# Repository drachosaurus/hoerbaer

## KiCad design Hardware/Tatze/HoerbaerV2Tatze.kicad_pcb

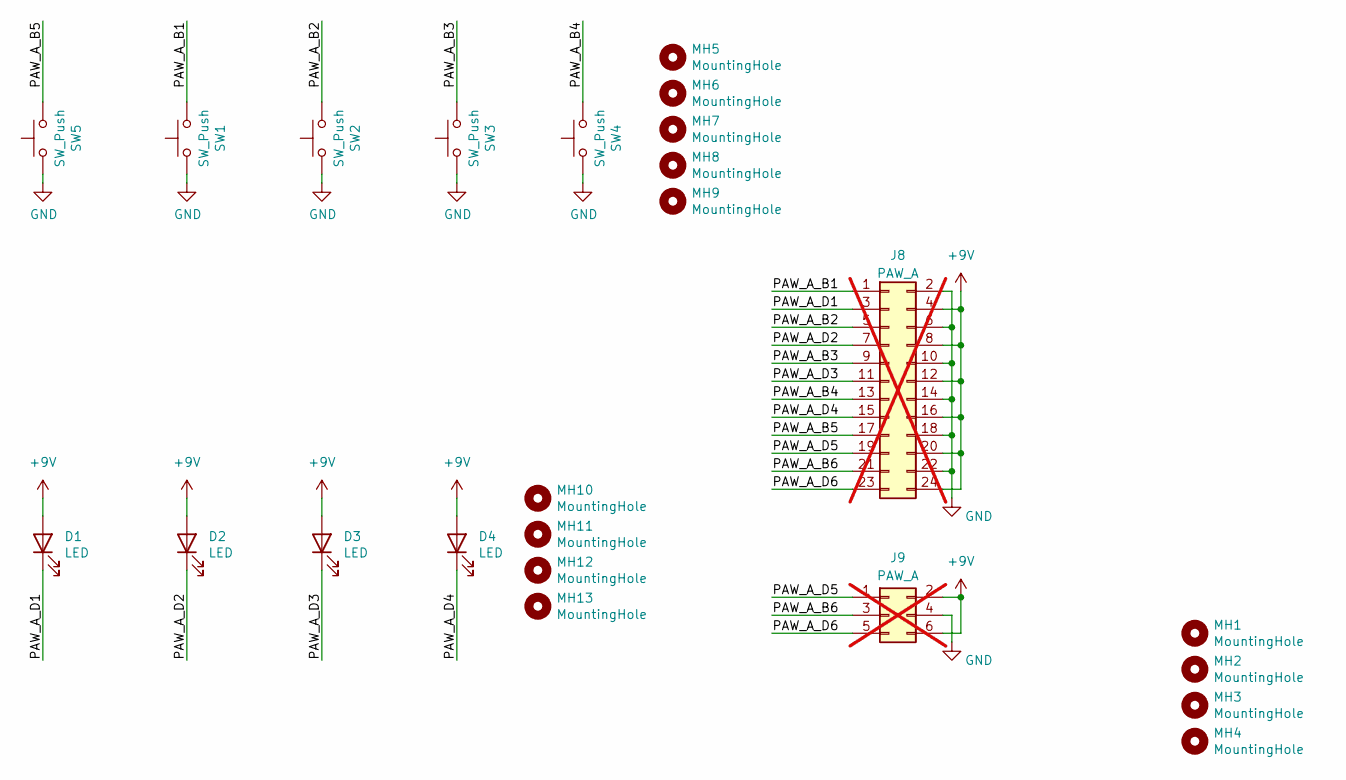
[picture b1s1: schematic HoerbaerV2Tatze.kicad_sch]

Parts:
D1, D2, D3, D4: LED; LED_D3.0mm
J8: PAW_A; PinHeader_2x12_P2.54mm_Vertical; JLCPCB Rotation Offset 90; not fitted
J9: PAW_A; PinHeader_2x03_P2.54mm_Vertical; JLCPCB Rotation Offset 90; not fitted
MH1, MH2, MH3, MH4: MountingHole; MountingHole_3.2mm_M3
MH5, MH6, MH7, MH8, MH9, MH10, MH11, MH12, MH13: MountingHole; MountingHole_2.1mm
SW1, SW2, SW3, SW4, SW5: SW_Push; SW_PUSH_6mm

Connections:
+9V: D1.2 (A), D2.2 (A), D3.2 (A), D4.2 (A), J8.4, J8.8, J8.12, J8.16, J8.20, J8.24, J9.2, J9.6
/PAW_A_B1: J8.1, SW1.2
/PAW_A_B2: J8.5, SW2.2
/PAW_A_B3: J8.9, SW3.2
/PAW_A_B4: J8.13, SW4.2
/PAW_A_B5: J8.17, SW5.2
/PAW_A_B6: J8.21, J9.3
/PAW_A_D1: D1.1 (K), J8.3
/PAW_A_D2: D2.1 (K), J8.7
/PAW_A_D3: D3.1 (K), J8.11
/PAW_A_D4: D4.1 (K), J8.15
/PAW_A_D5: J8.19, J9.1
/PAW_A_D6: J8.23, J9.5
GND: J8.2, J8.6, J8.10, J8.14, J8.18, J8.22, J9.4, SW1.1, SW2.1, SW3.1, SW4.1, SW5.1

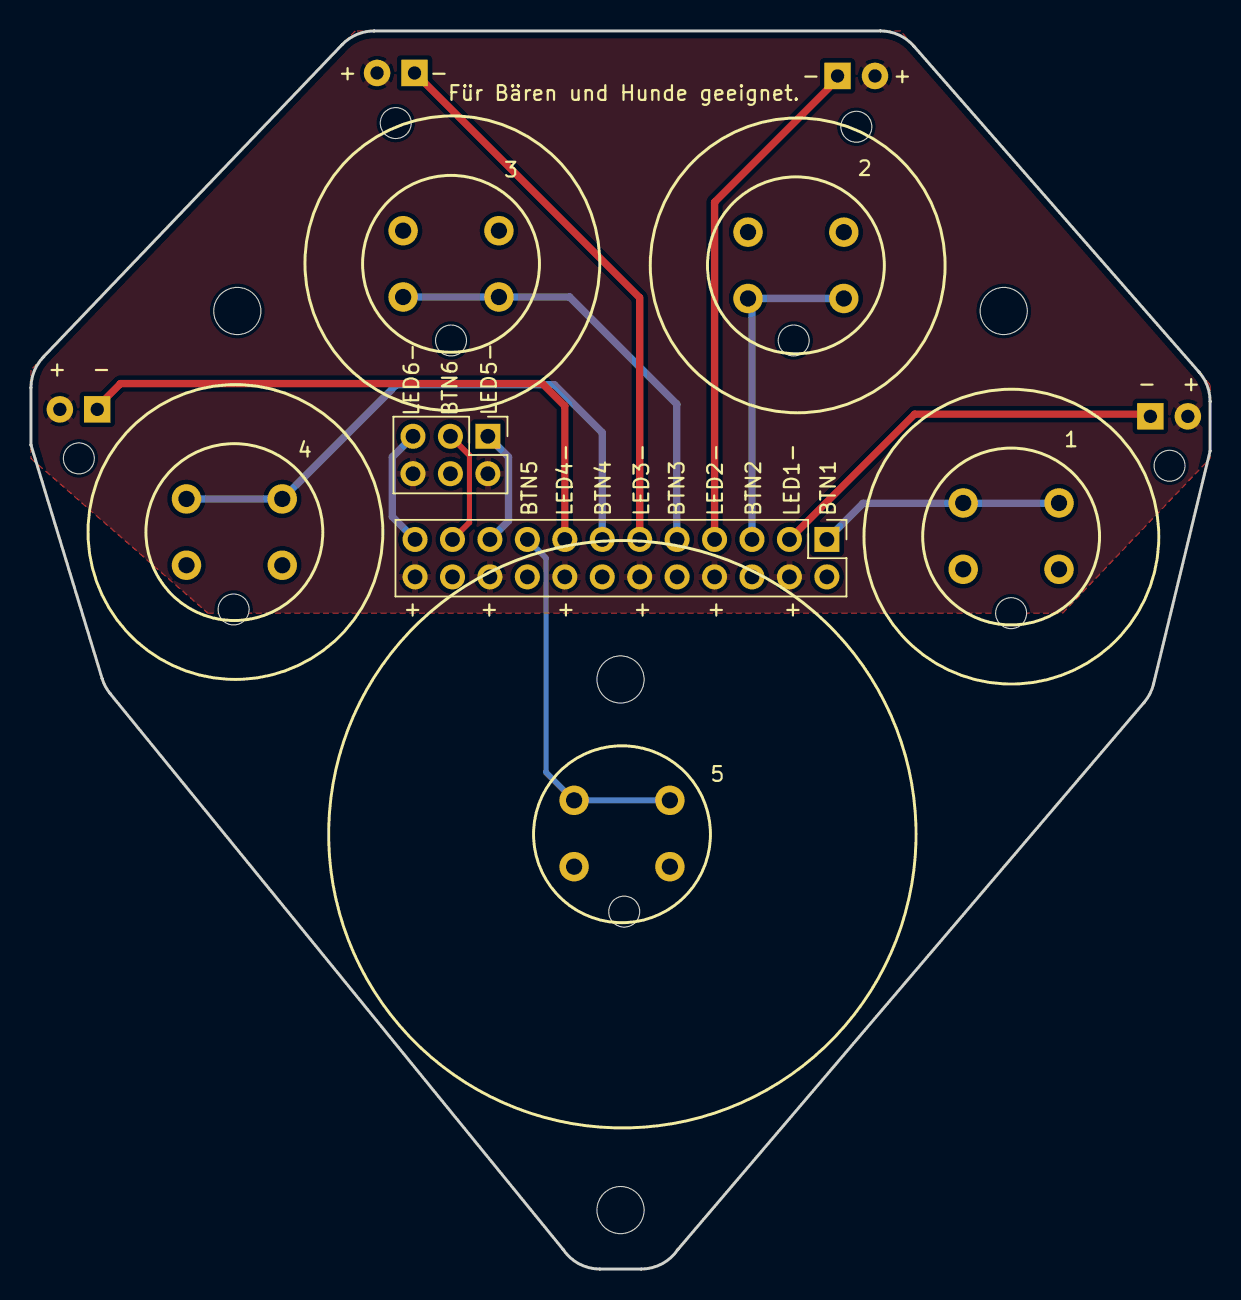
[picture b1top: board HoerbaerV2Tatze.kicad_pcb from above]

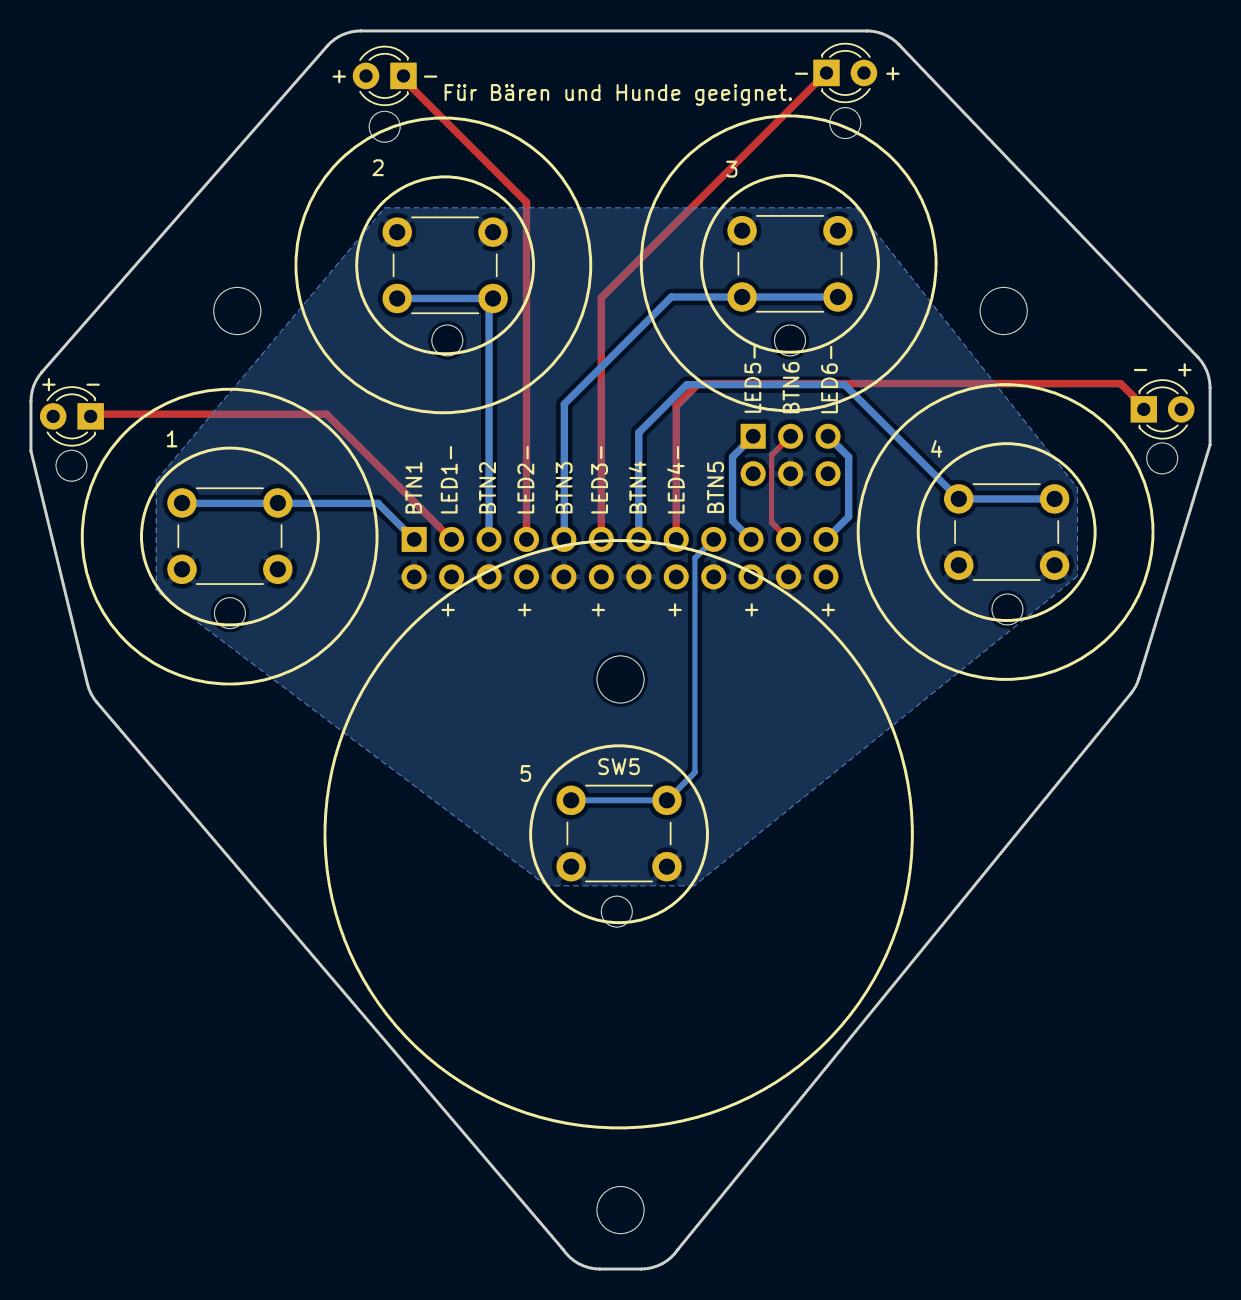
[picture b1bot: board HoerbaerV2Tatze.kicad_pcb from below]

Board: 2 copper layers, 80.0 x 84.0 mm, 24 parts (9 on the bottom side), 14 nets.

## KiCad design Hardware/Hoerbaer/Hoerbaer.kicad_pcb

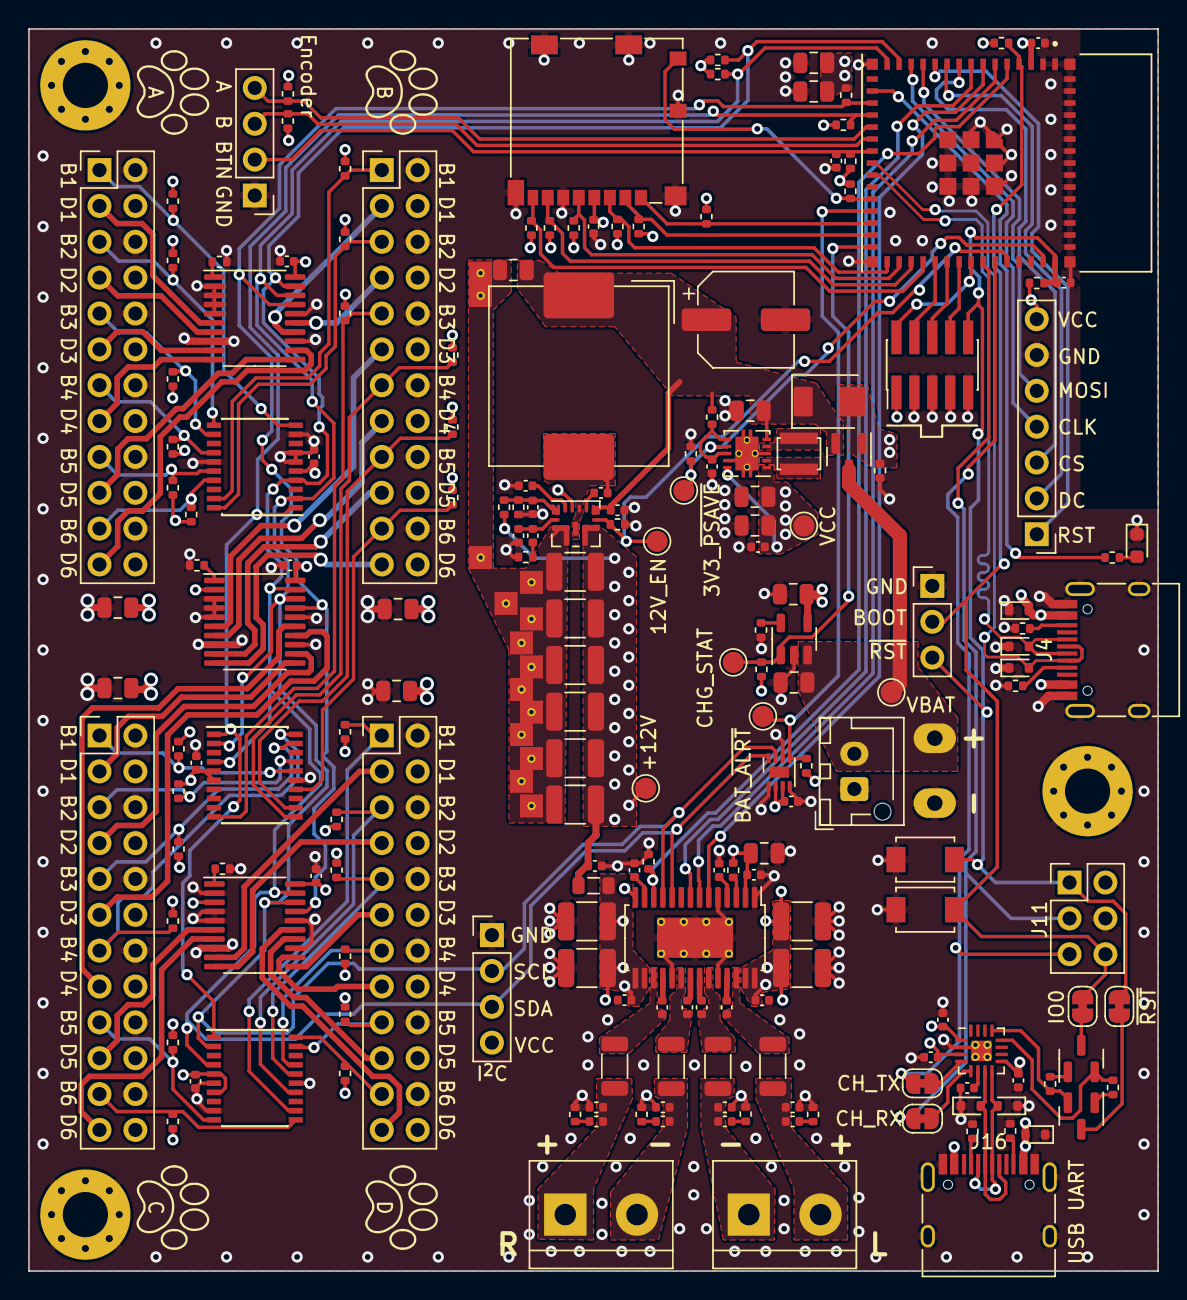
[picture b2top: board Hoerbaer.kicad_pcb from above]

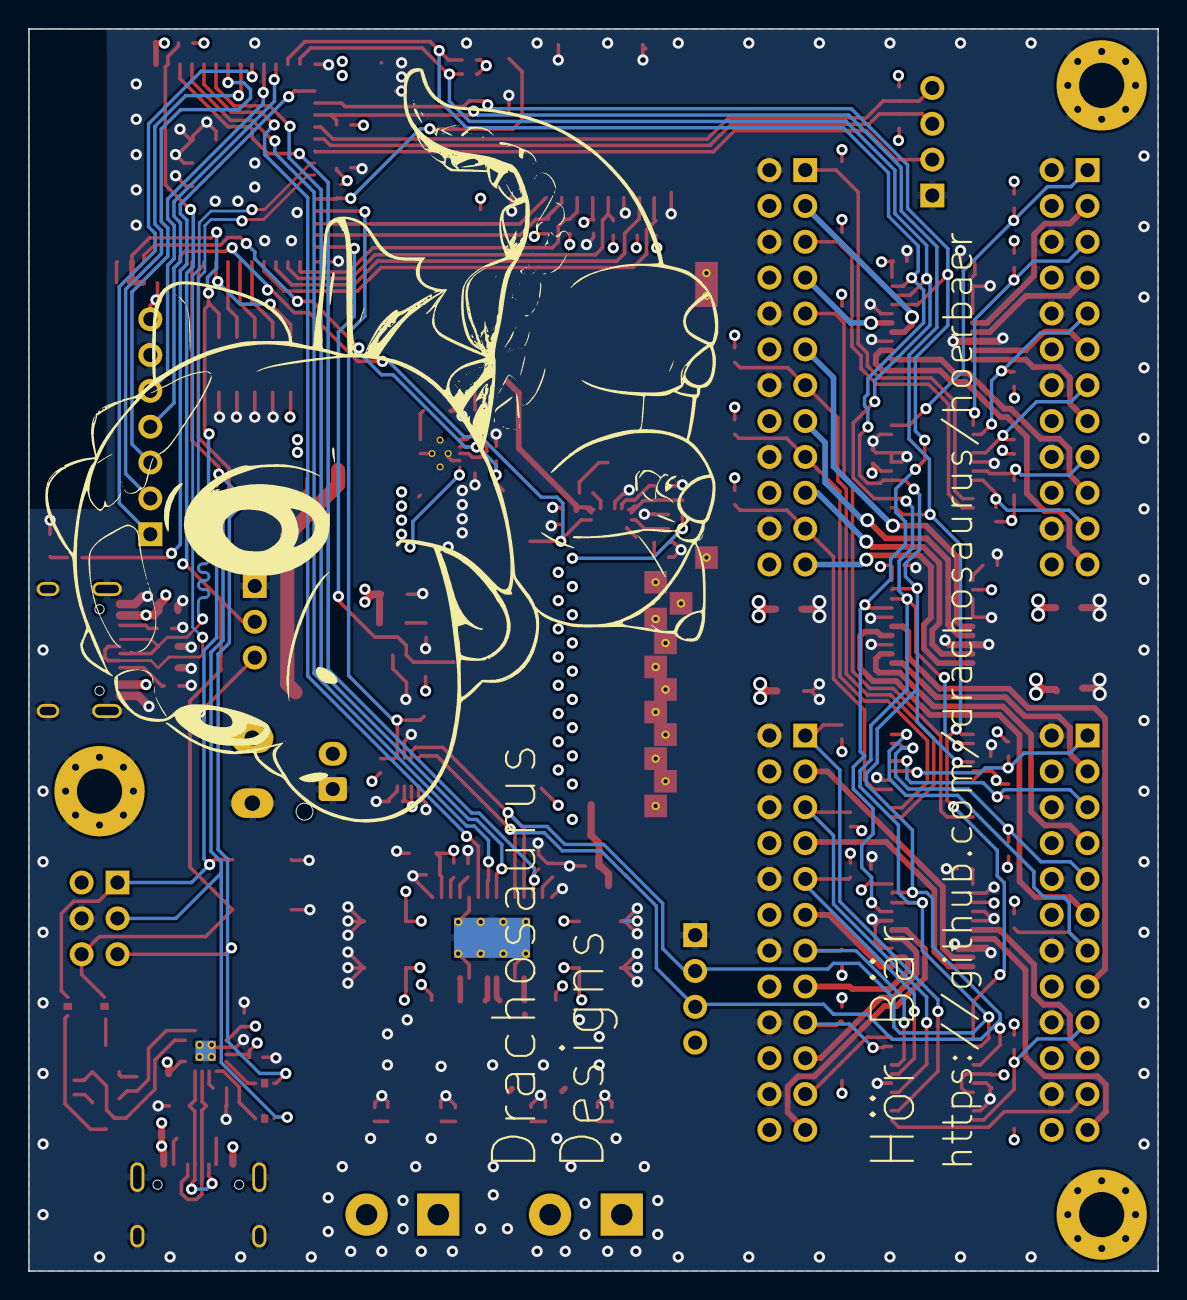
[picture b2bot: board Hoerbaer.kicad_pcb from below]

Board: 4 copper layers, 80.0 x 88.0 mm, 209 parts (14 on the bottom side), 143 nets.

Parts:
C1, C4, C5, C15, C20, C34, C35: 1µF, 10V; C_0402_1005Metric
C2, C3, C13, C14, C16, C22, C23, C24, C26, C65: 10µF; C_0805_2012Metric
C6, C7, C8, C9, C10, C11, C12, C19, C21, C25, C36, C43, C50, C58, C63, C64: 100nF; C_0402_1005Metric
C17, C18, C55: 4.7µF, 10V; C_0805_2012Metric
C27, C28, C29, C30, C31, C32, C37, C38, C44, C45: 22µF, low ESR; C_1210_3225Metric
C33, C46, C47, C48, C49, C51, C52, C53, C54: 2.2nF; C_0402_1005Metric
C39, C40, C41, C42: 220nF; C_0402_1005Metric
C56, C57: 1uF; C_0402_1005Metric
C59, C61: 27pF; C_0402_1005Metric
C60: 4.7nF; C_0402_1005Metric
C62: 47µF; CP_Elec_6.3x5.9
D1, D2, D5, D6, D7, D8: LESD5D5.0CT1G; D_SOD-523
D3: S54BF
D4: GREEN; LED_0603_1608Metric
FB1: 100Ω@100MHz, 3A; L_0805_2012Metric
FB2, FB3, FB4, FB5: 300Ω@100MHz, 3A; L_1206_3216Metric
H1, H2, H3: MountingHole_Pad; MountingHole_3.2mm_M3_Pad_Via
J1: I2C; PinHeader_1x04_P2.54mm_Vertical
J2: DISPLAY; PinHeader_1x07_P2.54mm_Vertical
J3: uSD; microSD_HC_Molex_104031-0811
J4: USB1; USB_C_Receptacle_HRO_TYPE-C-31-M-12
J5: ENCODER; PinHeader_1x04_P2.54mm_Vertical
J6: PAW_A; PinHeader_2x12_P2.54mm_Vertical
J7: PAW_B; PinHeader_2x12_P2.54mm_Vertical
J8: PAW_C; PinHeader_2x12_P2.54mm_Vertical
J9: PAW_D; PinHeader_2x12_P2.54mm_Vertical
J10: Battery 1S Li-Ion; SolderWire-0.5sqmm_1x02_P4.6mm_D0.9mm_OD2.1mm
J11: UART; PinHeader_2x03_P2.54mm_Vertical
J12: Battery 1S Li-Ion; JST_XH_B2B-XH-AM_1x02_P2.50mm_Vertical
J13: JTAG; PinHeader_2x05_P1.27mm_Vertical_SMD
J14: Speaker_L; TerminalBlock_bornier-2_P5.08mm
J15: Speaker_R; TerminalBlock_bornier-2_P5.08mm
J16: USB2_UART; USB_C_Receptacle_HRO_TYPE-C-31-M-12
J17: RST_BOOT; PinHeader_1x03_P2.54mm_Vertical
JP1: CH_TX; SolderJumper-2_P1.3mm_Bridged_RoundedPad1.0x1.5mm
JP2: CH_RX; SolderJumper-2_P1.3mm_Bridged_RoundedPad1.0x1.5mm
JP3: ~{RST}; SolderJumper-2_P1.3mm_Bridged_RoundedPad1.0x1.5mm
JP4: IO0; SolderJumper-2_P1.3mm_Bridged_RoundedPad1.0x1.5mm
L1: 2.2µH; L_Murata_LQH3NPN
L2: 4.7uH, 14A; L_TDK_SPM12565
NT1, NT2, NT3, NT4, NT5, NT6, NT7, NT8, NT9, NT10, NT11, NT12, NT13, NT14: GNDs; NetTie-2_Via
Q1: DMG3415UQ-7; SOT-23
Q5, Q6: S8050; SOT-23
R1, R2, R3, R4, R7, R8, R9, R10, R11, R12, R13, R14, R15, R16, R17, R18, R19, R20, R21, R22, R23, R24, R25, R26, R27, R28, R29, R30, R31, R32, R33, R34, R35, R36, R37, R38, R39, R40, R41, R42, R46, R50, R51, R52, R54, R61, R69, R70: 10kΩ; R_0402_1005Metric
R5, R6, R56, R67, R68: 5.1kΩ; R_0402_1005Metric
R43, R44, R45, R49: 2kΩ; R_0402_1005Metric
R47: 100Ω; R_0402_1005Metric
R48: 100kΩ; R_0402_1005Metric
R53: 191kΩ; R_0402_1005Metric
R55: 47kΩ; R_0402_1005Metric
R62: 4.7kΩ; R_0402_1005Metric
R63, R64, R65, R66: 68Ω; R_0402_1005Metric
SW1: RESET; SW_ TS-1088-AR02016
SW2: PROG; SW_ TS-1088-AR02016
TP4: VCC; TestPoint_Pad_D1.5mm
TP5: VBAT; TestPoint_Pad_D1.5mm
TP6: 3V3_~{PSAVE}; TestPoint_Pad_D1.5mm
TP7: 12V_EN; TestPoint_Pad_D1.5mm
TP8: CHG_STAT; TestPoint_Pad_D1.5mm
TP9: BAT_~{ALRT}; TestPoint_Pad_D1.5mm
TP10: +12V; TestPoint_Pad_D1.5mm
U1: ESP32 S3 MINI; XCVR_ESP32-S3-MINI-1-N8
U2, U3, U4: PCF8574APWR; SSOP-20_4.4x6.5mm_P0.65mm
U5, U6, U7: TLC59108xPW; TSSOP-20_4.4x6.5mm_P0.65mm
U8: MCP73831T-2ACI/OT (4.2V); SOT-23-5
U9: TPS63001; Texas_DRC0010J_ThermalVias
U10: TAS5805M; HTSSOP-28-1EP_4.4x9.7mm_P0.65mm_EP2.85x5.4mm_ThermalVias
U11: CH343P; QFN-16-1EP_3x3mm_P0.5mm_EP1.45x1.45mm_ThermalVias
U12: MAX17048G; TDFN-8-1EP_MAXIM
U13: TPS61288; Texas_VQFN-HR-20_3x2.5mm_P0.5mm_RQQ0011A

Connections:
+12V: C22.1, C23.1, C24.1, C27.1, C28.1, C29.1, C30.1, C31.1, C32.1, C33.1, C65.1, FB1.1, J6.4, J6.8, J6.12, J6.16, J6.20, J6.24, J7.4, J7.8, J7.12, J7.16, J7.20, J7.24, J8.4, J8.8, J8.12, J8.16, J8.20, J8.24, J9.4, J9.8, J9.12, J9.16, J9.20, J9.24, R53.1, TP10.1, U13.5 (VOUT)
+BATT: C17.1, C19.1, J10.2, J12.2, Q1.3 (D), TP5.1, U8.3 (VBAT), U12.2 (CELL), U12.3 (VDD)
/3V3_~PSAVE: R46.1, TP6.1, U1.44 (IO46), U9.7 (PS/SYNC)
/12V_EN: R52.1, TP7.1, U1.41 (IO45), U13.6 (EN)
/Audio/AMP_OUT_A+: C39.2, FB2.1, U10.26 (OUT_A+)
/Audio/AMP_OUT_A-: C40.2, FB3.1, U10.23 (OUT_A-)
/Audio/AMP_OUT_B+: C41.2, FB4.1, U10.17 (OUT_B+)
/Audio/AMP_OUT_B-: C42.2, FB5.1, U10.20 (OUT_B-)
/Audio/PVDD: C36.1, C37.1, C38.1, C43.1, C44.1, C45.1, FB1.2, U10.15 (PVDD), U10.16 (PVDD), U10.27 (PVDD), U10.28 (PVDD)
/Audio/SPEAKER_A+: C46.1, C51.1, FB2.2, J14.2
/Audio/SPEAKER_A-: C47.1, C52.1, FB3.2, J14.1
/Audio/SPEAKER_B+: C48.1, C53.1, FB4.2, J15.1
/Audio/SPEAKER_B-: C49.1, C54.1, FB5.2, J15.2
/BAT_~ALERT: R51.2, TP9.1, U1.27 (IO47), U12.5 (~ALRT)
/CHG_STAT: R50.2, TP8.1, U1.30 (IO48), U8.1 (STAT)
/CODEC_~PDN: R61.2, U1.5 (IO1), U10.12 (~PDN)
/DISP_CS: J2.3, U1.9 (IO5)
/DISP_DC: J2.2, U1.10 (IO6)
/DISP_RST: J2.1, U1.11 (IO7)
/ENC_A: J5.4, R8.2, U1.20 (IO16)
/ENC_B: J5.3, R10.2, U1.21 (IO17)
/ENC_BTN: C64.1, J5.2, R13.2, U1.22 (IO18)
/HBI/PAW_A_B1: J6.1, R19.2, U2.10 (P0)
/HBI/PAW_A_B2: J6.5, R22.2, U2.11 (P1)
/HBI/PAW_A_B3: J6.9, R25.2, U2.12 (P2)
/HBI/PAW_A_B4: J6.13, R28.2, U2.14 (P3)
/HBI/PAW_A_B5: J6.17, R31.2, U2.16 (P4)
/HBI/PAW_A_B6: J6.21, R34.2, U2.17 (P5)
/HBI/PAW_A_D1: J6.3, U5.6 (~OUT0)
/HBI/PAW_A_D2: J6.7, U5.7 (~OUT1)
/HBI/PAW_A_D3: J6.11, U5.9 (~OUT2)
/HBI/PAW_A_D4: J6.15, U5.10 (~OUT3)
/HBI/PAW_A_D5: J6.19, U5.11 (~OUT4)
/HBI/PAW_A_D6: J6.23, U5.12 (~OUT5)
/HBI/PAW_B_B1: J7.1, R37.2, U2.19 (P6)
/HBI/PAW_B_B2: J7.5, R40.2, U2.20 (P7)
/HBI/PAW_B_B3: J7.9, R20.2, U3.10 (P0)
/HBI/PAW_B_B4: J7.13, R23.2, U3.11 (P1)
/HBI/PAW_B_B5: J7.17, R26.2, U3.12 (P2)
/HBI/PAW_B_B6: J7.21, R29.2, U3.14 (P3)
/HBI/PAW_B_D1: J7.3, U5.14 (~OUT6)
/HBI/PAW_B_D2: J7.7, U5.15 (~OUT7)
/HBI/PAW_B_D3: J7.11, U6.6 (~OUT0)
/HBI/PAW_B_D4: J7.15, U6.7 (~OUT1)
/HBI/PAW_B_D5: J7.19, U6.9 (~OUT2)
/HBI/PAW_B_D6: J7.23, U6.10 (~OUT3)
/HBI/PAW_C_B1: J8.1, R32.2, U3.16 (P4)
/HBI/PAW_C_B2: J8.5, R35.2, U3.17 (P5)
/HBI/PAW_C_B3: J8.9, R38.2, U3.19 (P6)
/HBI/PAW_C_B4: J8.13, R41.2, U3.20 (P7)
/HBI/PAW_C_B5: J8.17, R21.2, U4.10 (P0)
/HBI/PAW_C_B6: J8.21, R24.2, U4.11 (P1)
/HBI/PAW_C_D1: J8.3, U6.11 (~OUT4)
/HBI/PAW_C_D2: J8.7, U6.12 (~OUT5)
/HBI/PAW_C_D3: J8.11, U6.14 (~OUT6)
/HBI/PAW_C_D4: J8.15, U6.15 (~OUT7)
/HBI/PAW_C_D5: J8.19, U7.6 (~OUT0)
/HBI/PAW_C_D6: J8.23, U7.7 (~OUT1)
/HBI/PAW_D_B1: J9.1, R27.2, U4.12 (P2)
/HBI/PAW_D_B2: J9.5, R30.2, U4.14 (P3)
/HBI/PAW_D_B3: J9.9, R33.2, U4.16 (P4)
/HBI/PAW_D_B4: J9.13, R36.2, U4.17 (P5)
/HBI/PAW_D_B5: J9.17, R39.2, U4.19 (P6)
/HBI/PAW_D_B6: J9.21, R42.2, U4.20 (P7)
/HBI/PAW_D_D1: J9.3, U7.9 (~OUT2)
/HBI/PAW_D_D2: J9.7, U7.10 (~OUT3)
/HBI/PAW_D_D3: J9.11, U7.11 (~OUT4)
/HBI/PAW_D_D4: J9.15, U7.12 (~OUT5)
/HBI/PAW_D_D5: J9.19, U7.14 (~OUT6)
/HBI/PAW_D_D6: J9.23, U7.15 (~OUT7)
/HBI_INT: R17.2, U1.19 (IO15), U2.1 (~INT), U3.1 (~INT), U4.1 (~INT)
/HBI_RST: R18.2, U1.18 (IO14), U5.17 (~RESET), U6.17 (~RESET), U7.17 (~RESET)
/I2C1_SCL: J1.2, R1.2, U1.15 (IO11), U2.2 (SCL), U3.2 (SCL), U4.2 (SCL), U5.18 (SCL), U6.18 (SCL), U7.18 (SCL), U10.11 (SCL), U12.7 (SCL)
/I2C1_SDA: J1.3, R2.2, U1.14 (IO10), U2.4 (SDA), U3.4 (SDA), U4.4 (SDA), U5.19 (SDA), U6.19 (SDA), U7.19 (SDA), U10.10 (SDA), U12.8 (SDA)
/I2S1_BCLK: U1.6 (IO2), U10.7 (SCLK)
/I2S1_DOUT: U1.8 (IO4), U10.8 (SDIN)
/I2S1_WS: U1.7 (IO3), U10.6 (LRCLK)
/JTAG_TCK: J13.4, U1.35 (IO39)
/JTAG_TDI: J13.8, U1.37 (IO41)
/JTAG_TDO: J13.6, U1.36 (IO40)
/JTAG_TMS: J13.2, U1.38 (IO42)
/MCU_IO0: J11.6, J17.2, JP4.1 (A), R16.2, SW2.2, U1.4 (IO0)
/MCU_RXD: J11.5, JP1.1 (A), U1.40 (RXD0)
/MCU_TXD: J11.3, JP2.1 (A), U1.39 (TXD0)
/MCU_~RST: C5.1, J11.1, J13.10, J17.3, JP3.1 (A), R15.2, SW1.2, U1.45 (EN)
/Power/3V3_L1: L1.1, U9.4 (L1)
/Power/3V3_L2: L1.2, U9.2 (L2)
/Power/12V_SW: C21.1, L2.2, U13.4 (SW), U13.9 (SW)
/Power/SWITCHER_VIN: C13.1, C25.1, C26.1, C62.1, D3.1 (K), L2.1, Q1.2 (S), R47.1, U9.5 (VIN), U13.7 (VIN)
/SD_CLK: J3.5 (CLK), R9.2, U1.32 (IO36)
/SD_CMD: J3.3 (CMD), R7.2, U1.31 (IO35)
/SD_D0: J3.7 (DAT0), R11.2, U1.33 (IO37)
/SD_D1: J3.8 (DAT1), R12.2, U1.34 (IO38)
/SD_D2: J3.1 (DAT2), R3.2, U1.28 (IO33)
/SD_D3: J3.2 (DAT3/CD), R4.2, U1.29 (IO34)
/SD_DET: J3.10 (DET_A), R14.2, U1.26 (IO26)
/SPI2_CLK: J2.4, U1.13 (IO9)
/SPI2_MOSI: J2.5, U1.12 (IO8)
/USB1_D+: D2.2 (A2), J4.A6 (D+), J4.B6 (D+), U1.24 (IO20)
/USB1_D-: D1.2 (A2), J4.A7 (D-), J4.B7 (D-), U1.23 (IO19)
/USB_UART/USB2_D+: D7.2 (A2), J16.A6 (D+), J16.B6 (D+), U11.7 (UD+)
/USB_UART/USB2_D-: D5.2 (A2), J16.A7 (D-), J16.B7 (D-), U11.8 (UD-)
/USB_UART/USB2_VBUS: C57.1, C63.1, D6.2 (A2), J16.A4 (VBUS), J16.A9 (VBUS), J16.B4 (VBUS), J16.B9 (VBUS), U11.3 (VDD5), U11.9 (VBUS)
/USB_UART/USB_UART_MCU_GPIO0_CHIP: JP4.2 (B), Q6.3 (C)
/USB_UART/USB_UART_MCU_~RST_CHIP: JP3.2 (B), Q5.3 (C)
/USB_UART/USB_UART_RXD_CHIP: JP2.2 (B), U11.5 (RXD)
/USB_UART/USB_UART_TXD_CHIP: JP1.2 (B), U11.4 (TXD)
GND: C1.2, C2.2, C3.2, C4.2, C5.2, C6.2, C7.2, C8.2, C9.2, C10.2, C11.2, C12.2, C13.2, C14.2, C15.2, C16.2, C17.2, C18.2, C19.2, C20.2, C22.2, C23.2, C24.2, C25.2, C33.2, C34.1, C35.1, C36.2, C37.2, C38.2, C43.2, C44.2, C45.2, C46.2, C47.2, C48.2, C49.2, C50.2, C55.2, C56.2, C57.2, C58.2, C59.2, C61.2, C62.2, C63.2, C64.2, C65.2, D1.1 (A1), D2.1 (A1), D4.1 (K), D5.1 (A1), D6.1 (A1), D7.1 (A1), D8.1 (A1), H1.1, H2.1, H3.1, J1.1, J2.6, J3.6 (VSS), J3.9 (DET_B), J3.11 (SHIELD), J4.A1 (GND), J4.A12 (GND), J4.B1 (GND), J4.B12 (GND), J4.S1 (SHIELD), J5.1, J6.2, J6.6, J6.10, J6.14, J6.18, J6.22, J7.2, J7.6, J7.10, J7.14, J7.18, J7.22, J8.2, J8.6, J8.10, J8.14, J8.18, J8.22, J9.2, J9.6, J9.10, J9.14, J9.18, J9.22, J10.1, J11.4, J12.1, J13.3, J13.5, J13.7, J13.9, J16.A1 (GND), J16.A12 (GND), J16.B1 (GND), J16.B12 (GND), J16.S1 (SHIELD), J17.1, NT1.1, NT2.1, NT3.1, NT4.1, NT5.1, NT6.1, NT7.1, NT8.1, NT9.1, NT10.1, NT11.1, NT12.1, NT13.1, NT14.1, R5.2, R6.2, R43.2, R44.2, R45.2, R46.2, R48.2, R49.2, R52.2, R54.2, R55.2, R61.1, R63.2, R64.2, R65.2, R66.2, R67.2, R68.2, SW1.1, SW2.1, U1.1 (GND), U1.2 (GND), U1.42 (GND), U1.43 (GND), U1.46 (GND), U1.47 (GND), U1.48 (GND), U1.49 (GND), U1.50 (GND), U1.51 (GND), U1.52 (GND), U1.53 (GND), U1.54 (GND), U1.55 (GND), U1.56 (GND), U1.57 (GND), U1.58 (GND), U1.59 (GND), U1.60 (GND), U1.61 (GND), U1.61_1 (GND), U1.61_2 (GND), U1.61_3 (GND), U1.61_4 (GND), U1.61_5 (GND), U1.61_6 (GND), U1.61_7 (GND), U1.61_8 (GND), U1.62 (GND), U1.63 (GND), U1.64 (GND), U1.65 (GND), U2.6 (A0), U2.7 (A1), U2.9 (A2), U2.15 (VSS), U3.7 (A1), U3.9 (A2), U3.15 (VSS), U4.6 (A0), U4.9 (A2), U4.15 (VSS), U5.2 (A0), U5.3 (A1), U5.4 (A2), U5.5 (A3), U5.8 (GND), U5.13 (GND), U5.16 (GND), U6.3 (A1), U6.4 (A2), U6.5 (A3), U6.8 (GND), U6.13 (GND), U6.16 (GND), U7.2 (A0), U7.4 (A2), U7.5 (A3), U7.8 (GND), U7.13 (GND), U7.16 (GND), U8.2 (VSS), U9.3 (PGND), U9.9 (GND), U9.11 (PGND), U10.1 (DGND), U10.5 (DGND), U10.14 (AGND), U10.19 (PGND), U10.24 (PGND), U10.29 (PAD), U11.2 (GND), U11.17 (GND), U12.1 (CTG), U12.4 (GND), U12.6 (QSTRT), U12.9 (PAD), U13.10 (AGND)
GNDPWR: C26.2, C27.2, C28.2, C29.2, C30.2, C31.2, C32.2, NT1.2, NT2.2, NT3.2, NT4.2, NT5.2, NT6.2, NT7.2, NT8.2, NT9.2, NT10.2, NT11.2, NT12.2, NT13.2, NT14.2, U13.3 (PGND)
unnamed: C51.2, R63.1
unnamed: C52.2, R64.1
unnamed: C53.2, R65.1
unnamed: C54.2, R66.1
unnamed: C60.2, R55.1
unnamed: D4.2 (A), R56.2
unnamed: J4.A5 (CC1), R5.1
unnamed: J4.B5 (CC2), R6.1
unnamed: J16.A5 (CC1), R67.1
unnamed: J16.B5 (CC2), R68.1
unnamed: Q5.1 (B), R69.2
unnamed: Q5.2 (E), R70.1, U11.13 (RTS)
unnamed: Q6.1 (B), R70.2
unnamed: Q6.2 (E), R69.1, U11.12 (DTR)
unnamed: R56.1, U1.17 (IO13)
unnamed: R43.1, U5.1 (REXT)
unnamed: R44.1, U6.1 (REXT)
unnamed: R45.1, U7.1 (REXT)
unnamed: R49.1, U8.5 (PROG)
unnamed: C12.1, R47.2, U9.6 (EN), U9.8 (VINA)
unnamed: R62.2, U10.3 (ADR/~FAULT)
unnamed: C35.2, U10.13 (AVDD)
unnamed: C39.1, U10.25 (BST_A+)
unnamed: C40.1, U10.22 (BST_A-)
unnamed: C41.1, U10.18 (BST_B+)
unnamed: C42.1, U10.21 (BST_B-)
unnamed: C34.2, U10.4 (VR_DIG)
unnamed: C58.1, U11.6 (V3)
unnamed: C21.2, U13.8 (BST)
unnamed: C60.1, C61.1, U13.2 (COMP)
unnamed: C59.1, R53.2, R54.1, U13.1 (FB)
unnamed: C20.1, U13.11 (VCC)
VBUS: C18.1, D3.2 (A), D8.2 (A2), J4.A4 (VBUS), J4.A9 (VBUS), J4.B4 (VBUS), J4.B9 (VBUS), Q1.1 (G), R48.1, U8.4 (VDD)
VCC: C1.1, C2.1, C3.1, C4.1, C6.1, C7.1, C8.1, C9.1, C10.1, C11.1, C14.1, C15.1, C16.1, C50.1, C55.1, C56.1, J1.4, J2.7, J3.4 (VDD), J11.2, J13.1, R1.1, R2.1, R3.1, R4.1, R7.1, R8.1, R9.1, R10.1, R11.1, R12.1, R13.1, R14.1, R15.1, R16.1, R17.1, R18.1, R19.1, R20.1, R21.1, R22.1, R23.1, R24.1, R25.1, R26.1, R27.1, R28.1, R29.1, R30.1, R31.1, R32.1, R33.1, R34.1, R35.1, R36.1, R37.1, R38.1, R39.1, R40.1, R41.1, R42.1, R50.1, R51.1, R62.1, TP4.1, U1.3 (3V3), U2.5 (VDD), U3.5 (VDD), U3.6 (A0), U4.5 (VDD), U4.7 (A1), U5.20 (VCC), U6.2 (A0), U6.20 (VCC), U7.3 (A1), U7.20 (VCC), U9.1 (VOUT), U9.10 (FB), U10.2 (DVDD), U11.1 (VIO)

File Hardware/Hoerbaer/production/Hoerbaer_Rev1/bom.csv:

Designator,Footprint,Quantity,Value,LCSC Part #
"C1, C15, C20, C34, C35, C4, C5",0402,7,"1µF, 10V",C726581
"C10, C11, C12, C19, C21, C25, C36, C43, C50, C58, C6, C63, C64, C7, C8, C9",0402,16,100nF,C458949
"C13, C14, C16, C2, C22, C23, C24, C26, C3, C65",0805,10,10µF,C6119932
"C17, C18, C55",0805,3,"4.7µF, 10V",C361188
"C27, C28, C29, C30, C31, C32, C37, C38, C44, C45",1210,10,"22µF, low ESR",C6120032
"C33, C46, C47, C48, C49, C51, C52, C53, C54",0402,9,2.2nF,C267415
"C39, C40, C41, C42",0402,4,220nF,C915854
"C56, C57",0402,2,1uF,C726581
"C59, C61",0402,2,27pF,C386133
C60,0402,1,4.7nF,C1517770
C62,CP_Elec_6.3x5.9,1,47µF,C110165
"D1, D2, D5, D6, D7, D8",D_SOD-523,6,LESD5D5.0CT1G,C383211
D3,S54BF,1,S54BF,C432789
D4,0603,1,GREEN,C72043
FB1,0805,1,"100Ω@100MHz, 3A",C316421
"FB2, FB3, FB4, FB5",1206,4,"300Ω@100MHz, 3A",C370090
J1,PinHeader_1x04_P2.54mm_Vertical,1,I2C,DNP
J11,PinHeader_2x03_P2.54mm_Vertical,1,UART,DNP
J12,JST_XH_B2B-XH-AM_1x02_P2.50mm_Vertical,1,Battery 1S Li-Ion,DNP
J13,PinHeader_2x05_P1.27mm_Vertical_SMD,1,JTAG,
J14,TerminalBlock_bornier-2_P5.08mm,1,Speaker_L,DNP
J15,TerminalBlock_bornier-2_P5.08mm,1,Speaker_R,DNP
J16,USB_C_Receptacle_HRO_TYPE-C-31-M-12,1,USB2_UART,C2765186
J17,PinHeader_1x03_P2.54mm_Vertical,1,RST_BOOT,DNP
J2,PinHeader_1x07_P2.54mm_Vertical,1,DISPLAY,DNP
J3,microSD_HC_Molex_104031-0811,1,Micro_SD_Card_Det1,C585350
J4,USB_C_Receptacle_HRO_TYPE-C-31-M-12,1,USB1,C2765186
J5,PinHeader_1x04_P2.54mm_Vertical,1,ENCODER,DNP
J6,PinHeader_2x12_P2.54mm_Vertical,1,PAW_A,DNP
J7,PinHeader_2x12_P2.54mm_Vertical,1,PAW_B,DNP
J8,PinHeader_2x12_P2.54mm_Vertical,1,PAW_C,DNP
J9,PinHeader_2x12_P2.54mm_Vertical,1,PAW_D,DNP
JP1,SolderJumper-2_P1.3mm_Bridged_RoundedPad1.0x1.5mm,1,CH_TX,
JP2,SolderJumper-2_P1.3mm_Bridged_RoundedPad1.0x1.5mm,1,CH_RX,
JP3,SolderJumper-2_P1.3mm_Bridged_RoundedPad1.0x1.5mm,1,~{RST},
JP4,SolderJumper-2_P1.3mm_Bridged_RoundedPad1.0x1.5mm,1,IO0,
L1,L_Murata_LQH3NPN,1,2.2µH,C341775
L2,L_TDK_SPM12565,1,"4.7uH, 14A",C2048059
Q1,SOT-23,1,DMG3415UQ-7,C459537
"Q5, Q6",SOT-23,2,S8050,C2150
"R1, R10, R11, R12, R13, R14, R15, R16, R17, R18, R19, R2, R20, R21, R22, R23, R24, R25, R26, R27, R28, R29, R3, R30, R31, R32, R33, R34, R35, R36, R37, R38, R39, R4, R40, R41, R42, R46, R50, R51, R52, R54, R61, R69, R7, R70, R8, R9",0402,48,10kΩ,C25744
"R43, R44, R45, R49",0402,4,2kΩ,C4109
R47,0402,1,100Ω,C25076
R48,0402,1,100kΩ,C25741
"R5, R56, R6, R67, R68",0402,5,5.1kΩ,C25905
R53,0402,1,191kΩ,C270632
R55,0402,1,47kΩ,C25792
R62,0402,1,4.7kΩ,C25900
"R63, R64, R65, R66",0402,4,68Ω,C25131
SW1,SW_ TS-1088-AR02016,1,RESET,C720477
SW2,SW_ TS-1088-AR02016,1,PROG,C720477
U1,XCVR_ESP32-S3-MINI-1-N8,1,ESP32 S3 MINI,
U10,HTSSOP-28-1EP_4.4x9.7mm_P0.65mm_EP2.85x5.4mm_ThermalVias,1,TAS5805M,C478472
U11,QFN-16-1EP_3x3mm_P0.5mm_EP1.45x1.45mm_ThermalVias,1,CH343P,C2846043
U12,TDFN-8-1EP_MAXIM,1,MAX17048G,C2682616
U13,Texas_VQFN-HR-20_3x2.5mm_P0.5mm_RQQ0011A,1,TPS61288,C5219223
"U2, U3, U4",SSOP-20_4.4x6.5mm_P0.65mm,3,PCF8574APWR,C94361
"U5, U6, U7",TSSOP-20_4.4x6.5mm_P0.65mm,3,TLC59108xPW,C130031
U8,SOT-23-5,1,MCP73831T-2ACI/OT (4.2V),C424093
U9,Texas_DRC0010J_ThermalVias,1,TPS63001,C28060

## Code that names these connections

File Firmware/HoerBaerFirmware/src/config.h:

#pragma once

#ifndef PINOUT_PCB_REV
// PCB Rev 2 (latest) is the default
#define PINOUT_PCB_REV 2
#endif

// Task priorities
#define TASK_PRIO_HBI_WORKER 2
#define TASK_STACK_SIZE_HBI_WORKER_WORDS (30 * 1024 / 4) // 30 kbytes
#define TASK_PRIO_BLE_WORKER 1
#define TASK_STACK_SIZE_BLE_WORKER_WORDS (10 * 1024 / 4) // 10 kbytes
#define TASK_PRIO_WS_UPDATE_WORKER 1
#define TASK_STACK_SIZE_WS_UPDATE_WORKER_WORDS (10 * 1024 / 4) // 10 kbytes
#define TASK_PRIO_RFID_WORKER 2
#define TASK_STACK_SIZE_RFID_WORKER_WORDS (30 * 1024 / 4) // 30 kbytes

// Well known SDCARD files
#define SDCARD_FILE_CONFIG "/config.json"
#define SDCARD_FILE_META_CACHE "/_metaCache.json"

// BLE IDs
#define BLE_SERVICE_UUID "4ed1ce10-a038-404e-9e93-64bc8d8a4753"
#define BLE_CHARACTERISTIC_POWER_UUID "bdb1d967-8a30-42fd-b035-0b65e15074ca"
#define BLE_CHARACTERISTIC_PLAYER_UUID "936bc2e0-2ba8-4a15-9c98-b82fcc308d22"
#define BLE_CHARACTERISTIC_NETWORK_UUID "14fbff44-b62b-4f75-91aa-aac6df208754"
#define BLE_CHARACTERISTIC_CONTROL_UUID "e3a1c5f0-7b2d-4c8a-9f3e-2d6b8a9e5c4f"
#define BLE_CHARACTERISTIC_PLAYER_CMD_UUID "f7a12580-4bc8-46c5-9f69-d7935c3a2b01"

// BLE characteristics update interval
#define BLE_CHARACTERISTICS_UPDATE_INTERVAL_MILLIS 1000

// Audio playing info update interval
#define AUDIO_PLAYING_INGO_UPDATE_INTERVAL_MILLIS 500

// I2C addresses
#define I2C_ADDR_LED_DRIVER1 0x40   // (R: 0x81, W: 0x80)
#define I2C_ADDR_LED_DRIVER2 0x41   // (R: 0x83, W: 0x82)
#define I2C_ADDR_LED_DRIVER3 0x42   // (R: 0x85, W: 0x84)
#define I2C_ADDR_IO_EXPANDER1 0x38  // (R: 0x71, W: 0x70)
#define I2C_ADDR_IO_EXPANDER2 0x39  // (R: 0x73, W: 0x72)
#define I2C_ADDR_IO_EXPANDER3 0x3A  // (R: 0x75, W: 0x74)
#define I2C_ADDR_AUDIO_CODEC 0x2C   // (R: 0x59, W: 0x58)
// 0x36 (R: 0x6d, W: 0x6c) -> Fuel gauge, set in the  MAX17048 library


// TODO: who is this?
// I2C device found at address 0x48 (R: 0x91, W: 0x90)
// I2C device found at address 0x4b (R: 0x97, W: 0x96)

// Power management
#define POWER_BATTERY_CHECK_INTERVAL_MILLIS 5000
#define POWER_SHUTDOWN_VOLTAGE 3.0f
#define POWER_PERIPHERIAL_STARTUP_DELAY 300

// PINOUT -----------------------------

#if PINOUT_PCB_REV == 2

    // I2C pins
    #define GPIO_I2C_SDA 10
    #define GPIO_I2C_SCL 11

    // Power pins
    #define GPIO_POWER_3V3_NPSAVE 45
    #define GPIO_POWER_HV_ENABLE 42
    #define GPIO_POWER_VCC_P_ENABLE 48
    #define GPIO_POWER_CHG_STAT 47

    // HBI pins
    #define GPIO_HBI_INPUT_INT 7
    #define GPIO_HBI_LEDDRIVER_RST 15 
    #define GPIO_HBI_ENCODER_A 4
    #define GPIO_HBI_ENCODER_B 5
    #define GPIO_HBI_ENCODER_BTN 6

    // RFID pins (SPI)
    #define GPIO_RFID_SS 8
    #define GPIO_RFID_MOSI 16
    #define GPIO_RFID_CLK 17
    #define GPIO_RFID_MISO 18
    #define GPIO_RFID_RST 2

    // Audio pins
    #define GPIO_AUDIO_BCLK 46
    #define GPIO_AUDIO_LRCLK 3
    #define GPIO_AUDIO_DOUT 9
    #define GPIO_AUDIO_CODEC_NPDN 14

    // SD card pins
    #ifndef SD_MODE_SDMMC
        #define SD_MODE_SDMMC
    #endif
    #define SDMMC_FREQ 40000
    #define GPIO_SD_CLK 13
    #define GPIO_SD_CMD 12
    #define GPIO_SD_D0 38
    #define GPIO_SD_D1 39
    #define GPIO_SD_D2 40
    #define GPIO_SD_D3 41
    #define GPIO_SD_DETECT 21

#endif
#if PINOUT_PCB_REV == 1

    // I2C pins
    #define GPIO_I2C_SDA 10
    #define GPIO_I2C_SCL 11

    // Power pins
    #define GPIO_POWER_3V3_NPSAVE 46
    #define GPIO_POWER_HV_ENABLE 45
    #define GPIO_POWER_CHG_STAT 48

    // HBI pins
    #define GPIO_HBI_INPUT_INT 15
    #define GPIO_HBI_LEDDRIVER_RST 14
    #define GPIO_HBI_ENCODER_A 16
    #define GPIO_HBI_ENCODER_B 17
    #define GPIO_HBI_ENCODER_BTN 18

    // RFID pins (SPI)
    #define GPIO_RFID_SS 8
    #define GPIO_RFID_MOSI 16
    #define GPIO_RFID_CLK 17
    #define GPIO_RFID_MISO 18
    #define GPIO_RFID_RST 2

    // Audio pins
    #define GPIO_AUDIO_BCLK 2
    #define GPIO_AUDIO_LRCLK 3
    #define GPIO_AUDIO_DOUT 4
    #define GPIO_AUDIO_CODEC_NPDN 1

    // SD card pins
    #ifndef SD_MODE_SPI
        #define SD_MODE_SPI
    #endif
    #define GPIO_SD_SCK 36
    #define GPIO_SD_DO 37
    #define GPIO_SD_DI 35
    #define GPIO_SD_CS 34
    #define GPIO_SD_DETECT 26

#endif

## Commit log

2023-11-12 Footprints, order numbers, ...
2023-11-12 Schematic, first idea
2023-11-12 More numbers, changed HBI input package, i2c addresses, layout.
2023-11-12 Nearly complete schematic with TLV61048 as 12V booster.
2023-11-12 Renamed JLCPCB attribute to LCSC (plugin search list)
2023-11-12 Drachosaurus added
2023-11-12 Adjos refdes silkscreen
2023-11-12 Resistor Order Numbers
2023-11-12 Order numbers
2023-11-12 Layout drc error free
2023-11-12 Fixed net tie ground plane issue.
2023-11-12 Added an additional connector. And silk screen designs.
2023-11-12 Many small corrections, changed connectors, ...
2023-11-12 DRC fixes
2023-11-12 Vias around the edge, more gnd vias under the ESP module.
2023-11-12 Production Files for Revision 1
2023-11-13 Fixed 1uF order number.
2023-12-03 Firmware setup (platformio)
2023-12-03 Last hw changes before v1
2023-12-06 Added sd card reverse adapter pcb
2023-12-06 Wire up some firmware structure.
2023-12-06 Fork TLC59108 lib (shared "Wire"), added initial LEDs code
2023-12-06 Fixed I2C addresses
2023-12-06 Setup input expanders
2023-12-06 lock semaphore when using i2c.
2023-12-07 Simple prototype case
2023-12-07 Added 3d model for USB footprint.
2023-12-10 Audio Progress... codec registers vs. I2S configuration.
2023-12-16 First tone!
2023-12-17 Config progress
2023-12-17 Load I/O config.
2023-12-17 HBI progress
2023-12-17 Refactored HBI to private -> member workaround
2023-12-17 WIP: slot configuration progress.
2025-02-27 Kicad 9 - additional notes
2025-02-27 Added audio i2s lib as submodule
2025-02-27 Logger with sema
2025-02-27 Audio player controls
2025-02-28 Basic sleep / wakeup
2025-02-28 Sleep / deep sleep
2025-02-28 Reset more
2025-03-10 Sleeping...
2025-03-14 USB msc v1 working
2025-03-14 USB mode when any button is pressed
2025-03-16 Charger
2025-03-16 Log file timestamp
2025-03-16 More notes
2025-03-16 timezone
2025-03-16 Used sd mmc 4-bit driver
2025-03-16 SDMMC fix
2025-03-23 Measurements
2025-03-23 Utility methods, some fixes
2025-03-23 HBI measurement
2025-03-24 WIP new hw rev
2025-03-24 Layout, mono-jumpers
2025-03-29 Layout rev 2 - without silkscreen
2025-03-29 Silkscreen, warnings, ...
2025-03-30 Added more jumper options.
2025-03-30 Check inductance for 9v - ok
2025-03-30 Tatze - positions
2025-03-30 Tatze grösser
2025-03-30 Löcher
2025-03-30 Usb Skew and production settings
2025-03-30 BOM FIxes
2025-03-31 Small fixes, last prod todos
2025-03-31 Production
2025-03-31 Step file of rev 2
2025-04-01 Layout fixes (production feedback)
2025-04-11 Layout fixes, production fixes
2025-04-11 Firmware prep for new pcb
2025-04-12 PSRAM fixes, latest arduino lib (PSRAM / Audio issue)
2025-04-12 System Audio (eleven labs)
2025-04-12 Explicit set SD card mode
2025-04-12 Reduce config to one file
2025-04-12 BLE bootstrapping
2025-04-13 Bootstrap protobuf for ble characteristics.
2025-04-13 Bootstrapped bluetooth client app
2025-04-18 Firmware progress - sd card fixes, mono mode, ...
2025-04-20 HBI mapping fixes
2025-04-20 Read ID3 tags
2025-04-20 ID3, metadata, save in cache file
2025-04-20 BLE player state
2025-04-20 BLE remote progress
2025-04-21 Wifi state
2025-04-26 Added more memory tracing
2025-04-27 Removed not working consts
2025-05-10 LED brightness, playing info, ...
2025-05-10 Disconnect handling
2025-05-10 Control app progress
2025-05-11 Player commands
2025-05-25 Fixed next / prev with many files -> use count and total from file cache
2025-10-25 control app wip
2025-10-25 Wire up RFID class
2025-10-25 RFID I2C implementation - runtime issue
2025-10-25 RFID tag works
2025-10-25 Refactored all strings to PSRAM
2025-10-25 Increase JSON decode buffer
2025-12-28 Brought over boilerplate, refactored to vite (instead of react scripts)
2025-12-28 Applied stitch prototype
2025-12-28 Web UI components ready
2025-12-28 Slots API and frontend call
2025-12-28 WebSocket state
2025-12-28 Wired up commands - still crashing
2025-12-28 Command pointer fixes
2025-12-28 PlaySlot
2025-12-28 UI and backend fixes
2025-12-28 Fixed id3 parser encoding and volume slider.
2025-12-28 SPIFFS and local WebUI.
2025-12-28 Some more fixes (duration, battery, ...)
2025-12-29 Refactored commands to rest call (avoiding fragmented message issues with safari)
2025-12-29 Small UI improvements
2025-12-29 Collapsible paws
2025-12-30 Fixed hostname transmission
